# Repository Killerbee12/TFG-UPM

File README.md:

# Sistema de Alimentación Portátil para Montura de Telescopio

**Trabajo Fin de Grado** — Grado en Ingeniería Electrónica de Comunicaciones  
ETSIST · Universidad Politécnica de Madrid (UPM)

---

## De qué va este proyecto

Cualquiera que haya hecho astrofotografía o astronomía visual en campo abierto sabe que la energía es un problema. Las monturas motorizadas, las cámaras y los accesorios necesitan alimentación estable durante horas, normalmente lejos de cualquier enchufe. La solución clásica es cargar con una batería de plomo-ácido, que pesa, ocupa y no te dice cuánta carga le queda realmente.

Este TFG propone una alternativa: un **sistema de alimentación portátil basado en baterías LiFePO4** (12.8V, 7.5Ah), más ligeras y seguras que el plomo, con electrónica dedicada para monitorizar el estado de carga real, gestionar la recarga y entregar una tensión de salida estable a la montura.

## Qué hace el sistema

- **Mide la carga real de la batería** usando un fuel gauge (BQ34Z100-G1) con tecnología Impedance Track, que compensa el envejecimiento de las celdas y mide temperatura con un termistor NTC.
- **Gestiona la recarga** con un cargador buck-boost BQ25792, compatible con USB-PD 3.0.
- **Estabiliza la tensión de salida** mediante un convertidor buck-boost TPS551892-Q1, preparado para los picos de corriente que generan los motores de la montura.
- **Coordina todo** desde un microcontrolador STM32F411 programado con FreeRTOS, que lee la telemetría por I2C y gestiona las tareas del sistema de forma concurrente.

## Diseño hardware

El hardware está diseñado en **KiCad** y separado en PCBs independientes para aislar ruidos electromagnéticos y facilitar la depuración:

1. **Battery Gauge (BMS)** — Circuito del BQ34Z100-G1 con divisor de tensión, shunt de corriente y sensor térmico.
2. **Battery Charger** — Circuito del BQ25792 con la electrónica de carga.
3. **Bloque de control** — MCU STM32F411, buses I2C y lectura de telemetría.

## Estructura del repositorio

```
├── Anteproyecto/          Documentos del anteproyecto (borradores, versión firmada, ejemplos y revisiones del tutor)
├── Archivos/              Datasheets de referencia consultados durante el diseño
├── Inventario/            Datasheets organizados por tipo de componente:
│   ├── Bateria/               Pack LiFePO4 12.8V 7.5Ah
│   ├── Battery_Charger/       BQ25792, BQ25690, LTC4020, etc.
│   ├── Battery_Gauge/         BQ34Z100-G1, BQ34110, BQ78350, etc.
│   ├── DC-DC_BuckBoost/       TPS551892-Q1, TPS55285, TPS63070, etc.
│   ├── Microcontrolador/      STM32F411 Discovery
│   ├── Bobina/
│   ├── Conectores/
│   ├── Diodos-zener/
│   ├── Resistencias/
│   └── Transistores/
├── Notas/                 Notas y documentación del proyecto (memoria, apuntes)
├── PCB/                   Diseños de PCB en KiCad
│   ├── Prototipo_2.0/        Prototipo inicial del battery gauge
│   └── Proyecto/              Diseños finales
│       ├── PCB_BatteryCharger/
│       └── PCB_BatteryGaulge/
├── STM32_project/         Firmware en C (STM32CubeIDE + FreeRTOS)
└── README.md
```

## Herramientas utilizadas

| Área | Herramienta |
|---|---|
| Esquemáticos y PCB | KiCad |
| Firmware | STM32CubeIDE (HAL + FreeRTOS) |
| Microcontrolador | STM32F411 Discovery |
| Documentación | Word / PDF |

## Estado del proyecto

Este repositorio recoge todo el proceso de desarrollo del TFG: desde los primeros borradores del anteproyecto hasta los diseños de PCB y el firmware. Es un proyecto en progreso.

---

*Nizar El Azeouzi Amine — ETSIST, Universidad Politécnica de Madrid*

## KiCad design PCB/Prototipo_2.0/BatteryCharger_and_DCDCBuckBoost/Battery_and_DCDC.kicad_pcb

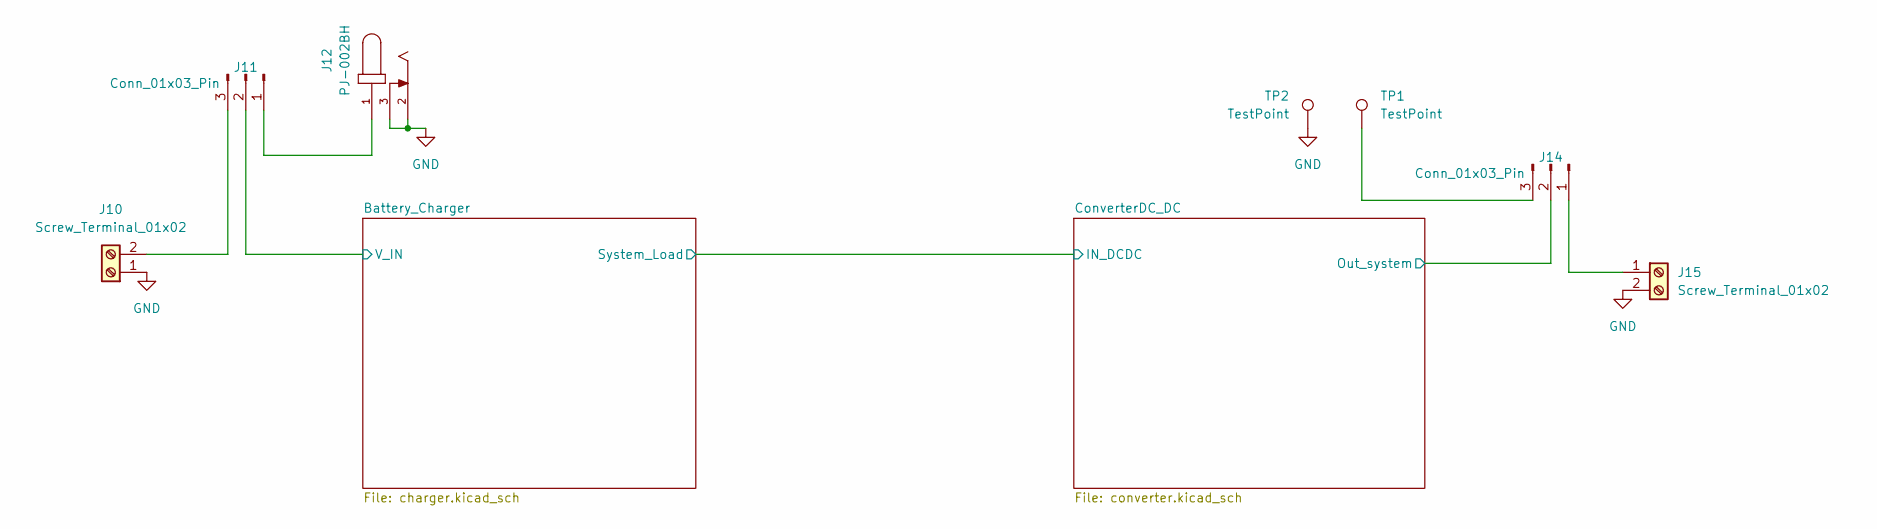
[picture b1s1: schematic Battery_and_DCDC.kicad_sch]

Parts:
J10, J15: Screw_Terminal_01x02; TerminalBlock_Phoenix_MKDS-1,5-2_1x02_P5.00mm_Horizontal
J11, J14: Conn_01x03_Pin; PinHeader_1x03_P2.54mm_Vertical
J12: PJ-002BH; CUI_PJ-002BH
TP1, TP2: TestPoint; TestPoint_Pad_3.0x3.0mm

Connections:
/Battery_Charger/V_IN: J11.2; also elsewhere on the board
/ConverterDC_DC/Out_system: J14.2; also elsewhere on the board
GND: J10.1, J12.2, J12.3, J15.2, TP2.1; also elsewhere on the board
unnamed: J10.2, J11.3
unnamed: J11.1, J12.1
unnamed: J14.1, J15.1
unnamed: J14.3, TP1.1

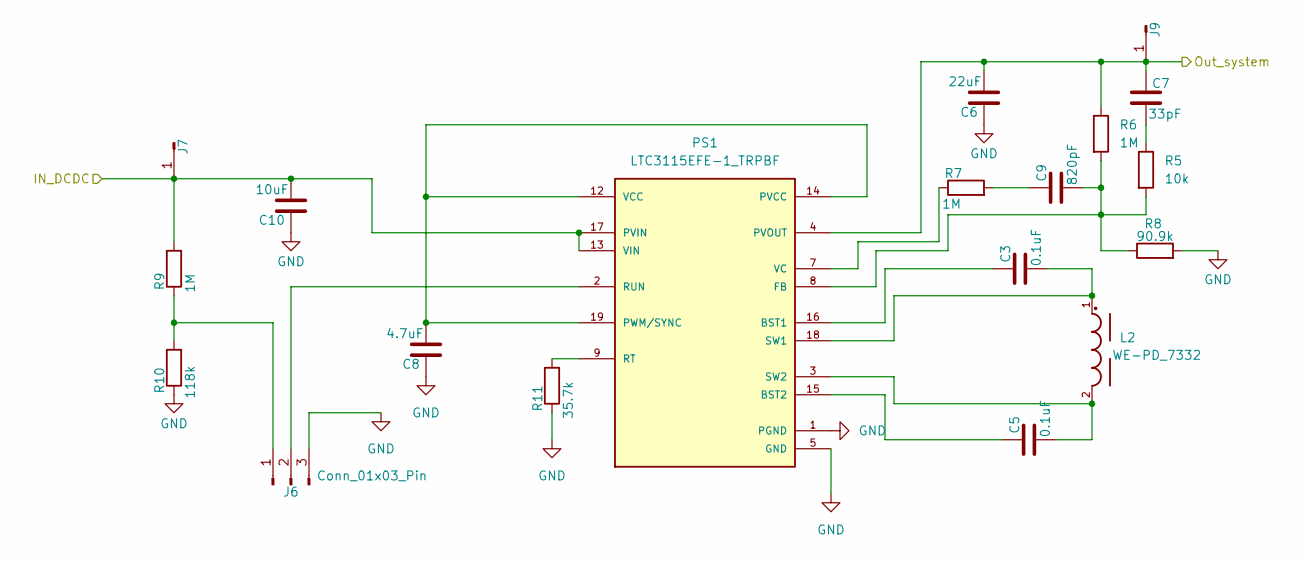
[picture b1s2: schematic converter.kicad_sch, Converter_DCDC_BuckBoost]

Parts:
C3, C5: 0.1uF; C_1206_3216Metric_Pad1.33x1.80mm_HandSolder
C6: 22uF; C_1206_3216Metric_Pad1.33x1.80mm_HandSolder
C7: 33pF; C_1206_3216Metric_Pad1.33x1.80mm_HandSolder
C8: 4.7uF; C_1206_3216Metric_Pad1.33x1.80mm_HandSolder
C9: 820pF; C_1206_3216Metric_Pad1.33x1.80mm_HandSolder
C10: 10uF; C_1206_3216Metric_Pad1.33x1.80mm_HandSolder
J6: Conn_01x03_Pin; PinHeader_1x03_P2.54mm_Vertical
J7, J9: Conn_01x01_Pin; PinHeader_1x01_P2.54mm_Vertical
L2: WE-PD_7332
PS1: LTC3115EFE-1_TRPBF; CONV_LTC3115EFE-1_TRPBF; PARTREV E
R5: 10k; R_1206_3216Metric_Pad1.30x1.75mm_HandSolder
R6, R7, R9: 1M; R_1206_3216Metric_Pad1.30x1.75mm_HandSolder
R8: 90.9k; R_1206_3216Metric_Pad1.30x1.75mm_HandSolder
R10: 118k; R_1206_3216Metric_Pad1.30x1.75mm_HandSolder
R11: 35.7k; R_1206_3216Metric_Pad1.30x1.75mm_HandSolder

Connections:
/Battery_Charger/System_Load: C10.1, J7.1, PS1.13 (VIN), PS1.17 (PVIN), R9.2; also elsewhere on the board
/ConverterDC_DC/Out_system: C6.1, C7.2, J9.1, PS1.4 (PVOUT), R6.1; also elsewhere on the board
GND: C6.2, C8.2, C10.2, J6.3, PS1.1 (PGND), PS1.5 (GND), PS1.6 (GND), PS1.10 (PGND), PS1.11 (PGND), PS1.20 (PGND), PS1.21 (PGND), R8.2, R10.1, R11.1; also elsewhere on the board
unnamed: C7.1, R5.1
unnamed: C9.2, R7.2
unnamed: J6.1, R9.1, R10.2
unnamed: J6.2, PS1.2 (RUN)
unnamed: C3.2, PS1.16 (BST1)
unnamed: C5.2, PS1.15 (BST2)
unnamed: C9.1, PS1.8 (FB), R5.2, R6.2, R8.1
unnamed: C8.1, PS1.12 (VCC), PS1.14 (PVCC), PS1.19 (PWM/SYNC)
unnamed: PS1.9 (RT), R11.2
unnamed: C3.1, L2.1, PS1.18 (SW1)
unnamed: C5.1, L2.2, PS1.3 (SW2)
unnamed: PS1.7 (VC), R7.1

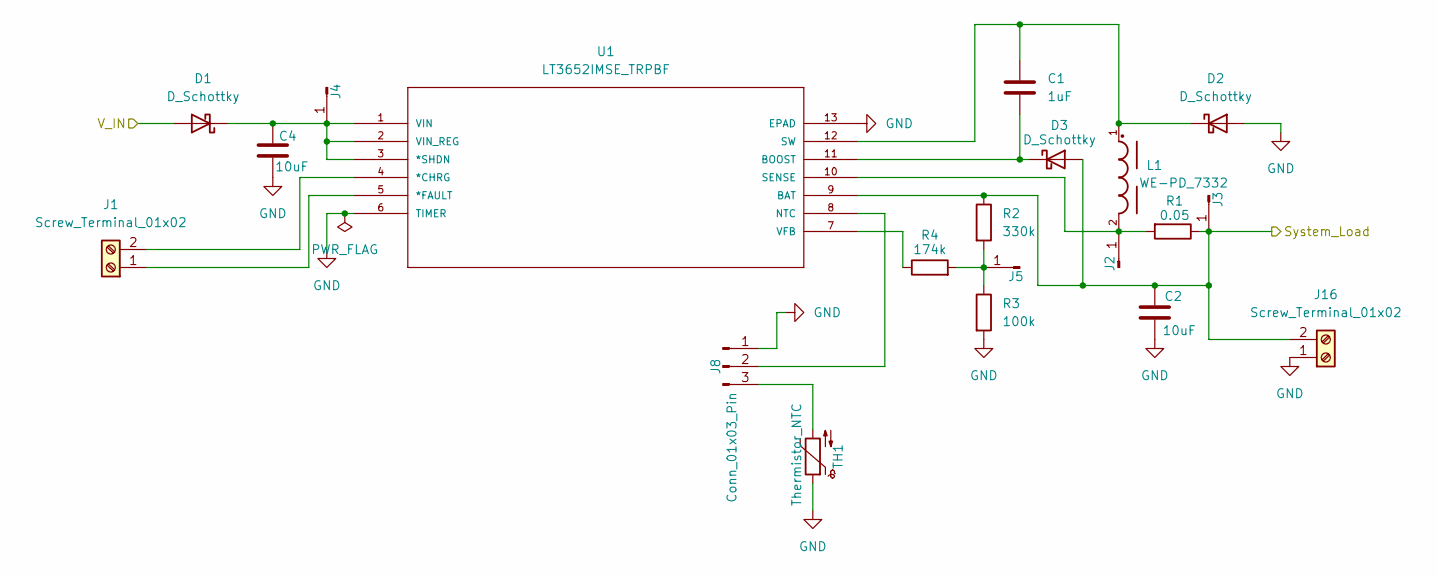
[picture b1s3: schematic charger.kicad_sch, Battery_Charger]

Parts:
C1: 1uF; C_1206_3216Metric_Pad1.33x1.80mm_HandSolder
C2, C4: 10uF; C_1206_3216Metric_Pad1.33x1.80mm_HandSolder
D1, D2: D_Schottky; D_SMB
D3: D_Schottky; D_SOD-123
J1, J16: Screw_Terminal_01x02; TerminalBlock_Phoenix_MKDS-1,5-2_1x02_P5.00mm_Horizontal
J2, J3, J4, J5: Conn_01x01_Pin; PinHeader_1x01_P2.54mm_Vertical
J8: Conn_01x03_Pin; PinHeader_1x03_P2.54mm_Vertical
L1: WE-PD_7332
R1: 0.05; R_1206_3216Metric_Pad1.30x1.75mm_HandSolder
R2: 330k; R_1206_3216Metric_Pad1.30x1.75mm_HandSolder
R3: 100k; R_1206_3216Metric_Pad1.30x1.75mm_HandSolder
R4: 174k; R_1206_3216Metric_Pad1.30x1.75mm_HandSolder
TH1: Thermistor_NTC; R_Axial_DIN0204_L3.6mm_D1.6mm_P5.08mm_Horizontal
U1: LT3652IMSE_TRPBF; MSOP-12_MSE; MANUFACTURER_PART_NUMBER lt3652imse#pbf

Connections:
/Battery_Charger/System_Load: C2.2, D3.2 (A), J3.1, J16.2, R1.1, R2.1, U1.9 (BAT); also elsewhere on the board
/Battery_Charger/V_IN: D1.2 (A); also elsewhere on the board
GND: C2.1, C4.1, D2.2 (A), J8.1, J16.1, R3.2, TH1.1, U1.6 (TIMER), U1.13 (EPAD); also elsewhere on the board
unnamed: C4.2, D1.1 (K), J4.1, U1.1 (VIN), U1.2 (VIN_REG), U1.3 (*SHDN)
unnamed: C1.2, D2.1 (K), L1.1, U1.12 (SW)
unnamed: C1.1, D3.1 (K), U1.11 (BOOST)
unnamed: J1.1, U1.5 (*FAULT)
unnamed: J1.2, U1.4 (*CHRG)
unnamed: J2.1, L1.2, R1.2, U1.10 (SENSE)
unnamed: J5.1, R2.2, R3.1, R4.2
unnamed: J8.2, U1.8 (NTC)
unnamed: J8.3, TH1.2
unnamed: R4.1, U1.7 (VFB)

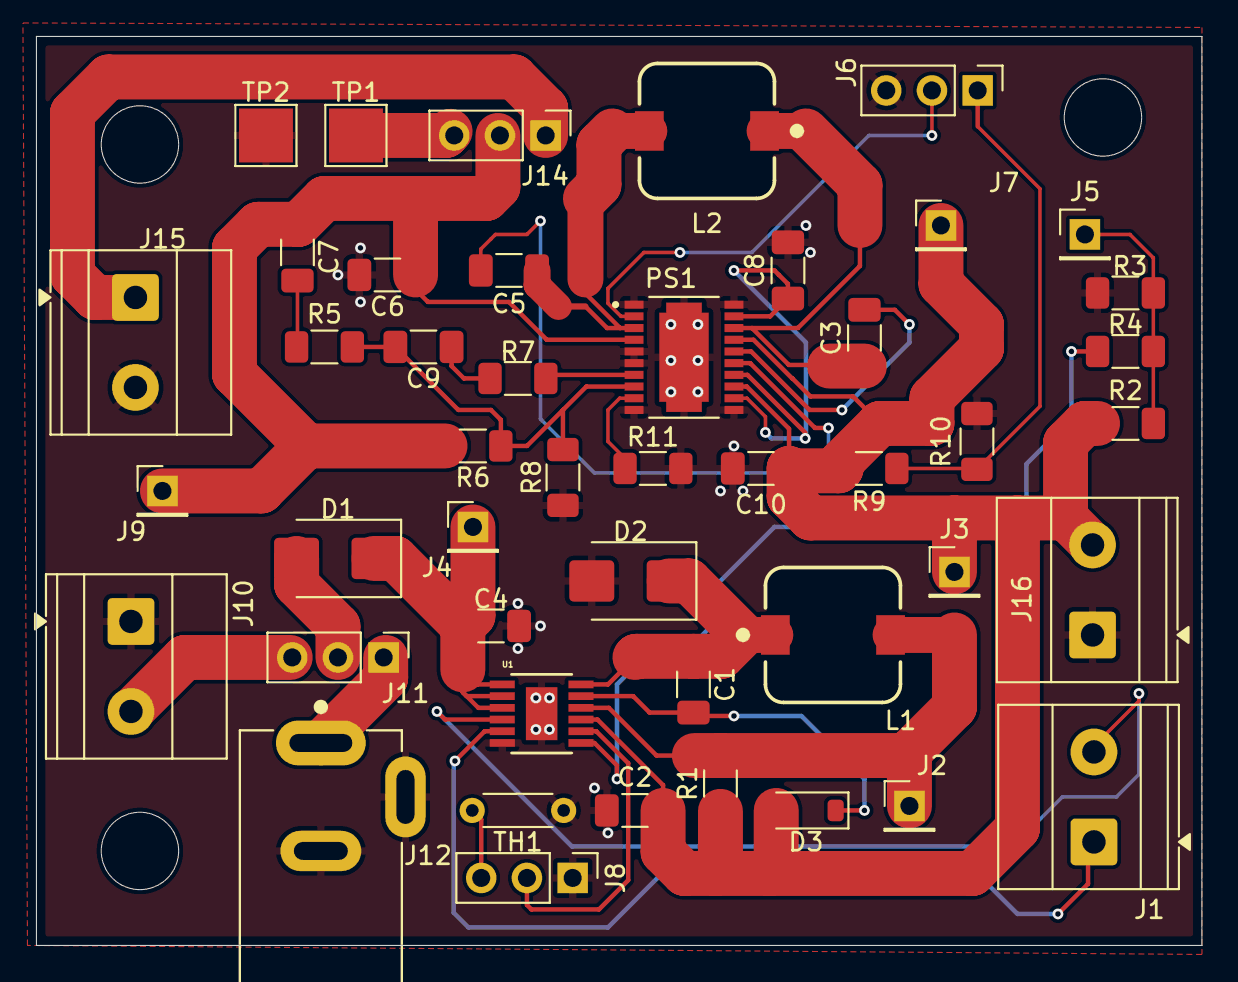
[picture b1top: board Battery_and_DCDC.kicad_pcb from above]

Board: 2 copper layers, 64.8 x 50.5 mm, 49 parts (0 on the bottom side), 30 nets.

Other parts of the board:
M1, M1#2, M1#3: MountingHole_4.3mm_M4

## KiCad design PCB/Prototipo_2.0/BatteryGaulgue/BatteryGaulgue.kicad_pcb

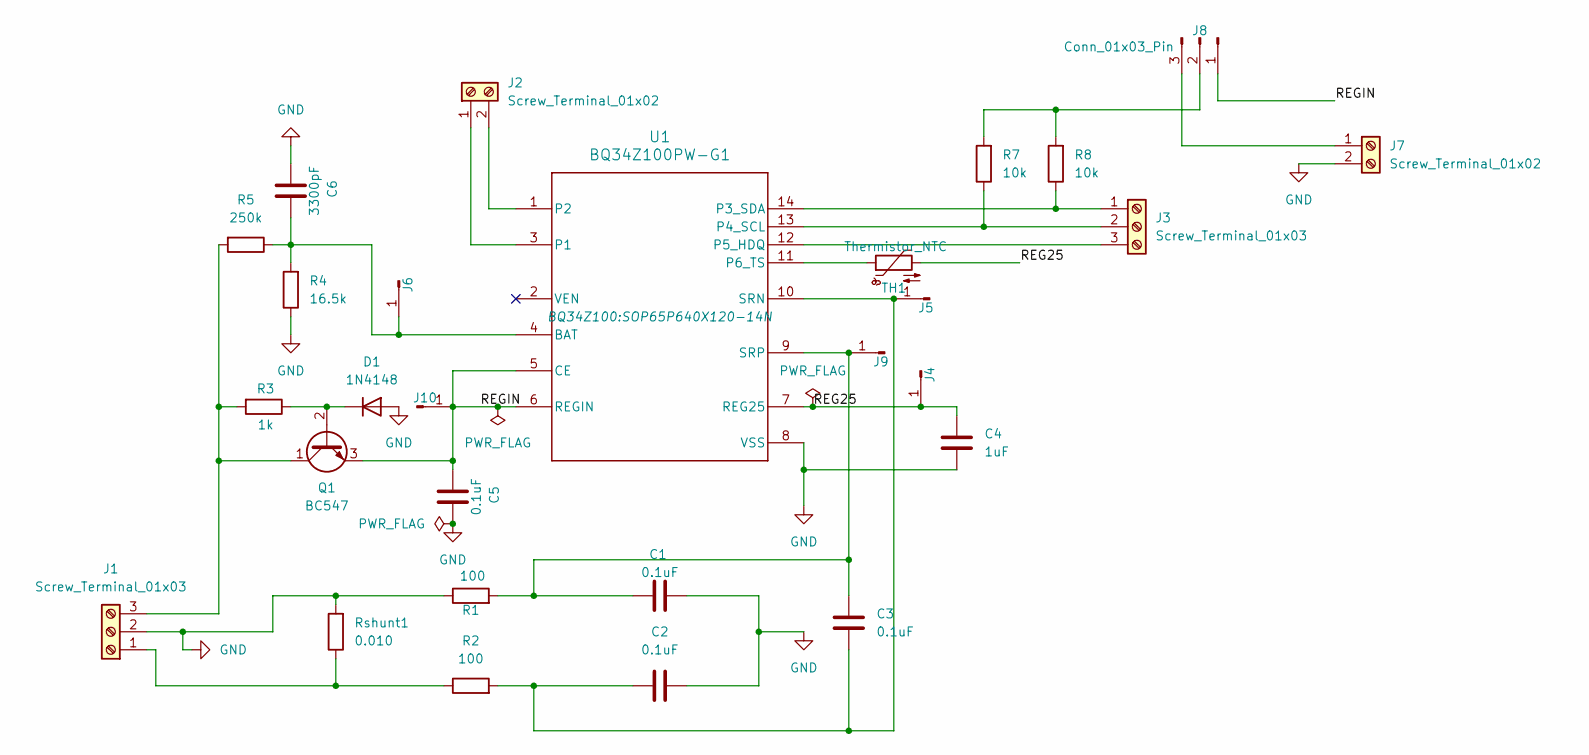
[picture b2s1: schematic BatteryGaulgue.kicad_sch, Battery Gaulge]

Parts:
C1, C2, C3, C5: 0.1uF; C_0805_2012Metric_Pad1.18x1.45mm_HandSolder
C4: 1uF; C_0805_2012Metric_Pad1.18x1.45mm_HandSolder
C6: 3300pF; C_0805_2012Metric_Pad1.18x1.45mm_HandSolder
D1: 1N4148; D_DO-35_SOD27_P7.62mm_Horizontal
J1, J3: Screw_Terminal_01x03; TerminalBlock_Phoenix_MKDS-1,5-3_1x03_P5.00mm_Horizontal
J2, J7: Screw_Terminal_01x02; TerminalBlock_Phoenix_MKDS-1,5-2_1x02_P5.00mm_Horizontal
J4, J5, J6, J9, J10: Conn_01x01_Pin; PinHeader_1x01_P2.54mm_Vertical
J8: Conn_01x03_Pin; PinHeader_1x03_P2.54mm_Vertical
Q1: BC547; TO-92_Inline
R1, R2: 100; R_1206_3216Metric_Pad1.30x1.75mm_HandSolder
R3: 1k; R_1206_3216Metric_Pad1.30x1.75mm_HandSolder
R4: 16.5k; R_1206_3216Metric_Pad1.30x1.75mm_HandSolder
R5: 250k; R_1206_3216Metric_Pad1.30x1.75mm_HandSolder
R7, R8: 10k; R_1206_3216Metric_Pad1.30x1.75mm_HandSolder
Rshunt1: 0.010; R_2512_6332Metric_Pad1.40x3.35mm_HandSolder
TH1: Thermistor_NTC; R_Axial_DIN0204_L3.6mm_D1.6mm_P5.08mm_Horizontal
U1: BQ34Z100PW-G1; SOP65P640X120-14N

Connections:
/REG25: C4.2, J4.1, TH1.2, U1.7 (REG25)
/REGIN: C5.2, J8.1, J10.1, Q1.3 (E), U1.5 (CE), U1.6 (REGIN)
GND: C1.1, C2.1, C4.1, C5.1, C6.2, D1.2 (A), J1.2, J7.2, R1.1, R4.1, Rshunt1.2, U1.8 (VSS)
unnamed: D1.1 (K), Q1.2 (B), R3.1
unnamed: J1.1, R2.1, Rshunt1.1
unnamed: J1.3, Q1.1 (C), R3.2, R5.2
unnamed: J2.1, U1.3 (P1)
unnamed: J2.2, U1.1 (P2)
unnamed: J3.1, R8.1, U1.14 (P3_SDA)
unnamed: J3.2, R7.1, U1.13 (P4_SCL)
unnamed: J3.3, U1.12 (P5_HDQ)
unnamed: C2.2, C3.2, J5.1, R2.2, U1.10 (SRN)
unnamed: C6.1, J6.1, R4.2, R5.1, U1.4 (BAT)
unnamed: J7.1, J8.3
unnamed: J8.2, R7.2, R8.2
unnamed: C1.2, C3.1, J9.1, R1.2, U1.9 (SRP)
unnamed: TH1.1, U1.11 (P6_TS)

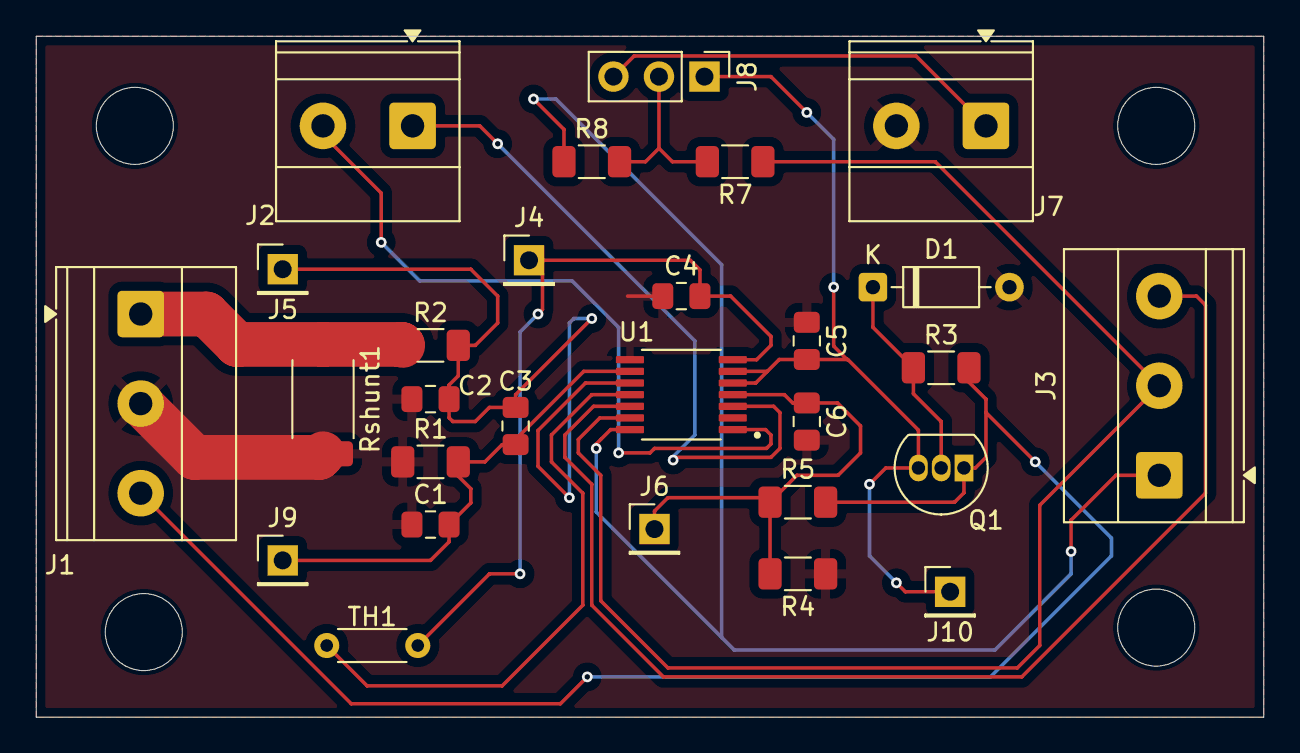
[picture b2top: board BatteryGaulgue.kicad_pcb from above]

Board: 2 copper layers, 68.5 x 38.0 mm, 32 parts (0 on the bottom side), 17 nets.

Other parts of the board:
M1, M2, M3, M4: MountingHole_4.3mm_M4

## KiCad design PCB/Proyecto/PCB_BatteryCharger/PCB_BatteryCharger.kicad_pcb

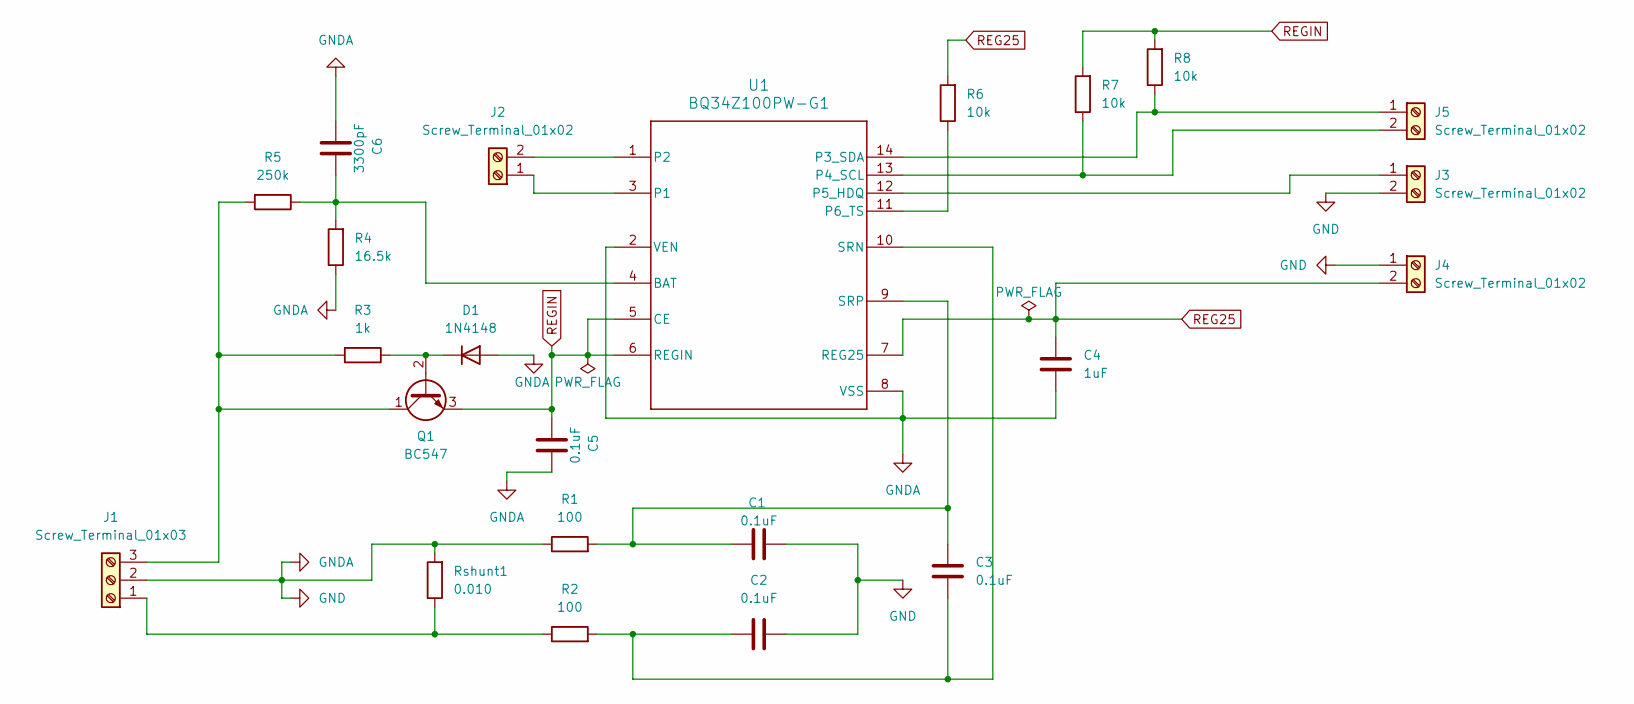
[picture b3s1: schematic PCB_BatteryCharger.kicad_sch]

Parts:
C1, C2, C3, C5: 0.1uF; C_Rect_L7.0mm_W3.5mm_P5.00mm
C4: 1uF; C_Rect_L7.0mm_W3.5mm_P5.00mm
C6: 3300pF; C_Rect_L7.0mm_W3.5mm_P5.00mm
D1: 1N4148; D_DO-35_SOD27_P7.62mm_Horizontal
J1: Screw_Terminal_01x03; TerminalBlock_Phoenix_MKDS-1-3-3.81_1x03_P3.81mm_Horizontal
J2, J3, J4, J5: Screw_Terminal_01x02; TerminalBlock_Phoenix_MKDS-1-2-3.81_1x02_P3.81mm_Horizontal
Q1: BC547; TO-92_Inline
R1, R2: 100; R_Axial_DIN0207_L6.3mm_D2.5mm_P10.16mm_Horizontal
R3: 1k; R_Axial_DIN0207_L6.3mm_D2.5mm_P10.16mm_Horizontal
R4: 16.5k; R_Axial_DIN0207_L6.3mm_D2.5mm_P10.16mm_Horizontal
R5: 250k; R_Axial_DIN0207_L6.3mm_D2.5mm_P10.16mm_Horizontal
R6, R7, R8: 10k; R_Axial_DIN0207_L6.3mm_D2.5mm_P10.16mm_Horizontal
Rshunt1: 0.010; R_2512_6332Metric_Pad1.40x3.35mm_HandSolder
U1: BQ34Z100PW-G1; PW0014A_N

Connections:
GND: C1.1, C2.1, C4.1, C5.1, C6.2, D1.2 (A), J1.2, J3.2, J4.1, R1.1, R4.1, Rshunt1.2, U1.2 (VEN), U1.8 (VSS)
unnamed: D1.1 (K), Q1.2 (B), R3.1
unnamed: J1.1, R2.1, Rshunt1.1
unnamed: J1.3, Q1.1 (C), R3.2, R5.2
unnamed: J2.1, U1.3 (P1)
unnamed: J2.2, U1.1 (P2)
unnamed: J3.1, U1.12 (P5_HDQ)
unnamed: J5.1, R8.1, U1.14 (P3_SDA)
unnamed: J5.2, R7.1, U1.13 (P4_SCL)
unnamed: C6.1, R4.2, R5.1, U1.4 (BAT)
unnamed: R6.1, U1.11 (P6_TS)
unnamed: C2.2, C3.2, R2.2, U1.10 (SRN)
unnamed: C1.2, C3.1, R1.2, U1.9 (SRP)
REG25: C4.2, J4.2, R6.2, U1.7 (REG25)
REGIN: C5.2, Q1.3 (E), R7.2, R8.2, U1.5 (CE), U1.6 (REGIN)

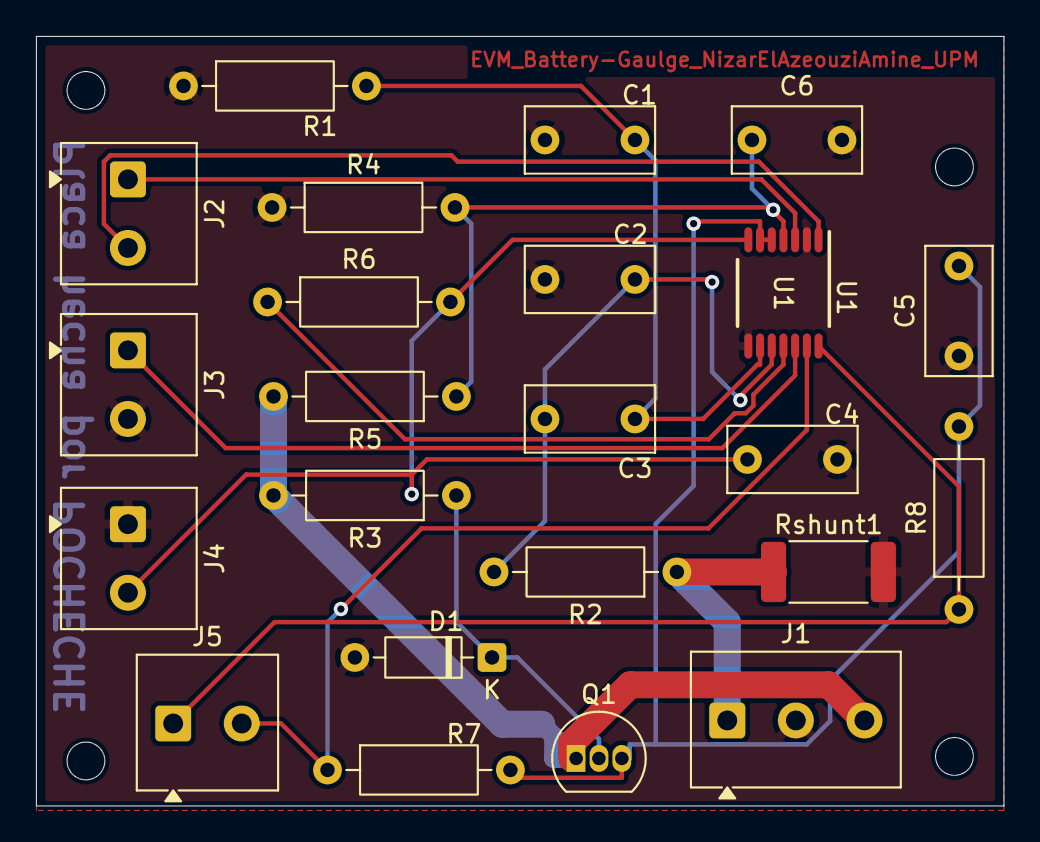
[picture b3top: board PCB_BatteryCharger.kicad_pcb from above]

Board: 2 copper layers, 53.8 x 42.8 mm, 27 parts (0 on the bottom side), 15 nets.

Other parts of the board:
H1, H2, H3, H4: MountingHole_2.1mm

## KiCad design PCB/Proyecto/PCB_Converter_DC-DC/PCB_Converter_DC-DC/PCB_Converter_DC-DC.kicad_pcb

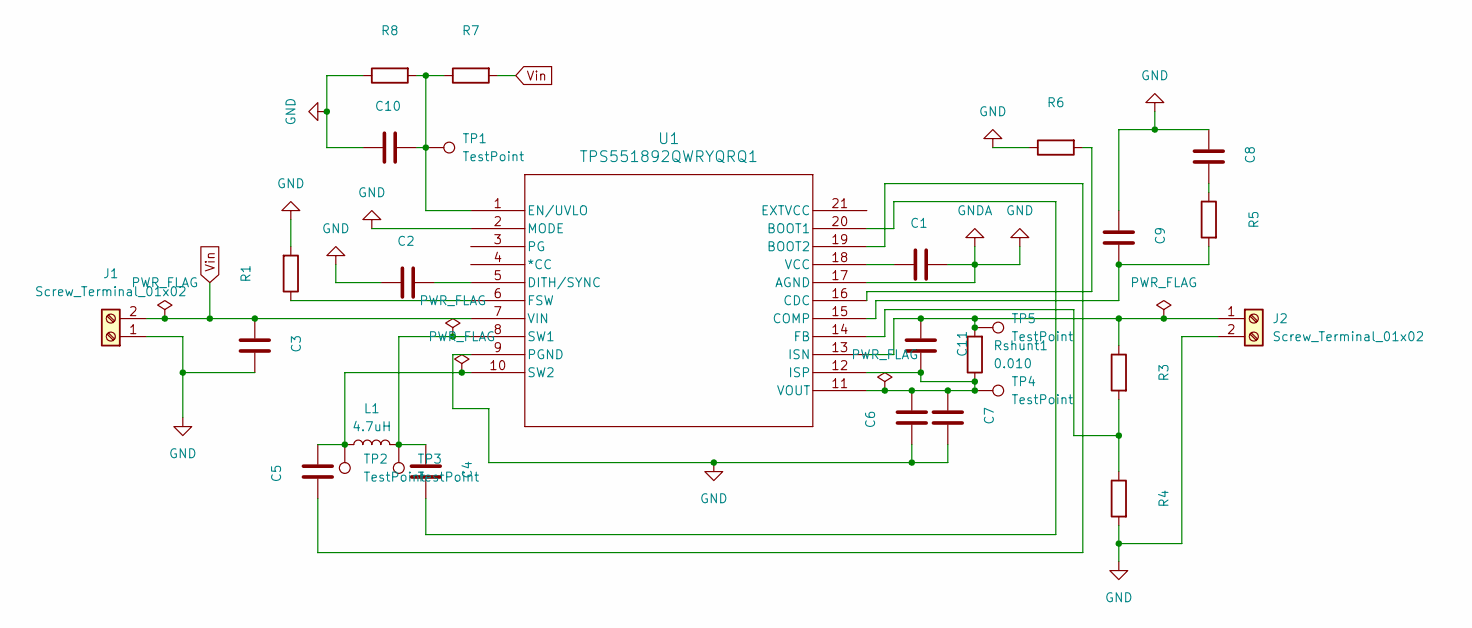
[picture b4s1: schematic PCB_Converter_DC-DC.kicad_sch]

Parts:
C1, C2, C3, C4, C5, C6, C7, C8, C9, C10, C11: C_Rect_L7.0mm_W3.5mm_P5.00mm
J1, J2: Screw_Terminal_01x02; TerminalBlock_Phoenix_MKDS-1-2-3.81_1x02_P3.81mm_Horizontal
L1: 4.7uH; L_Radial_D10.0mm_P5.00mm_Fastron_07M
R1, R3, R4, R5, R6, R7, R8: R_Axial_DIN0207_L6.3mm_D2.5mm_P10.16mm_Horizontal
Rshunt1: 0.010; R_2512_6332Metric_Pad1.40x3.35mm_HandSolder
TP1, TP2, TP3, TP4, TP5: TestPoint; TestPoint_THTPad_D2.0mm_Drill1.0mm
U1: TPS551892QWRYQRQ1; VQFN21_RYQ_TEX

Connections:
GND: C1.1, C2.2, C3.1, C6.2, C7.1, C8.2, C9.2, C10.2, J1.1, J2.2, R1.2, R4.2, R6.1, R8.1, U1.2 (MODE), U1.9 (PGND), U1.17 (AGND)
unnamed: C8.1, R5.1
unnamed: C11.2, J2.1, R3.1, Rshunt1.2, TP5.1, U1.13 (ISN)
unnamed: C4.1, U1.20 (BOOT1)
unnamed: C5.2, U1.19 (BOOT2)
unnamed: R6.2, U1.16 (CDC)
unnamed: C9.1, R5.2, U1.15 (COMP)
unnamed: C2.1, U1.5 (DITH/SYNC)
unnamed: C10.1, R7.1, R8.2, TP1.1, U1.1 (EN/UVLO)
unnamed: R3.2, R4.1, U1.14 (FB)
unnamed: R1.1, U1.6 (FSW)
unnamed: C6.1, C7.2, C11.1, Rshunt1.1, TP4.1, U1.11 (VOUT), U1.12 (ISP)
unnamed: C4.2, L1.2, TP3.1, U1.8 (SW1)
unnamed: C5.1, L1.1, TP2.1, U1.10 (SW2)
unnamed: C1.2, U1.18 (VCC)
Vin: C3.2, J1.2, R7.2, U1.7 (VIN)

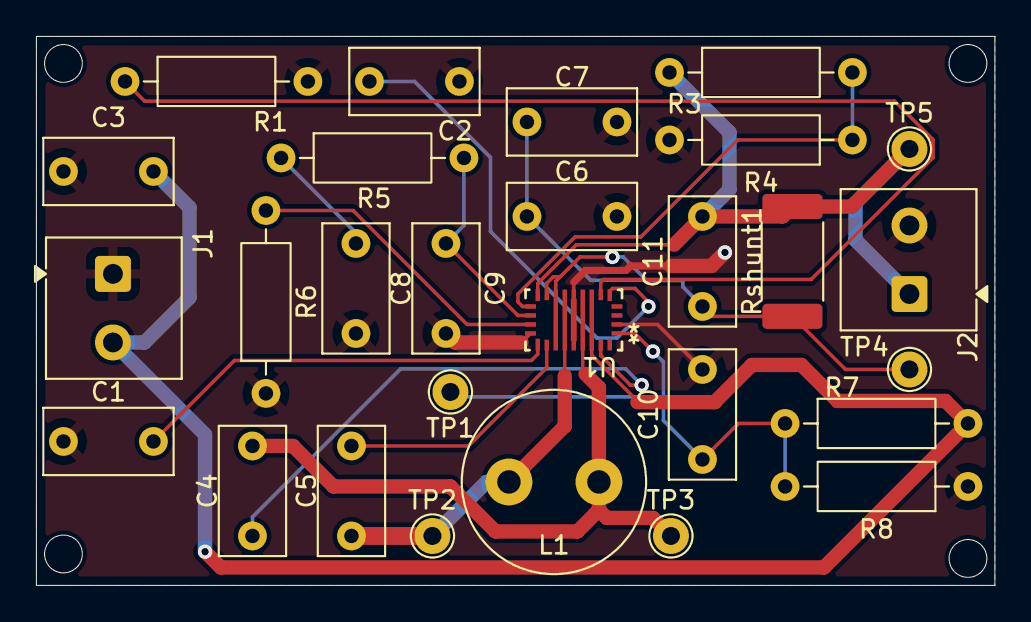
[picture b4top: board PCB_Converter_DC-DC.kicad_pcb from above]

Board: 2 copper layers, 53.2 x 30.5 mm, 32 parts (0 on the bottom side), 16 nets.

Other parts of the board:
H2, H3, H4, H5: MountingHole_2.1mm

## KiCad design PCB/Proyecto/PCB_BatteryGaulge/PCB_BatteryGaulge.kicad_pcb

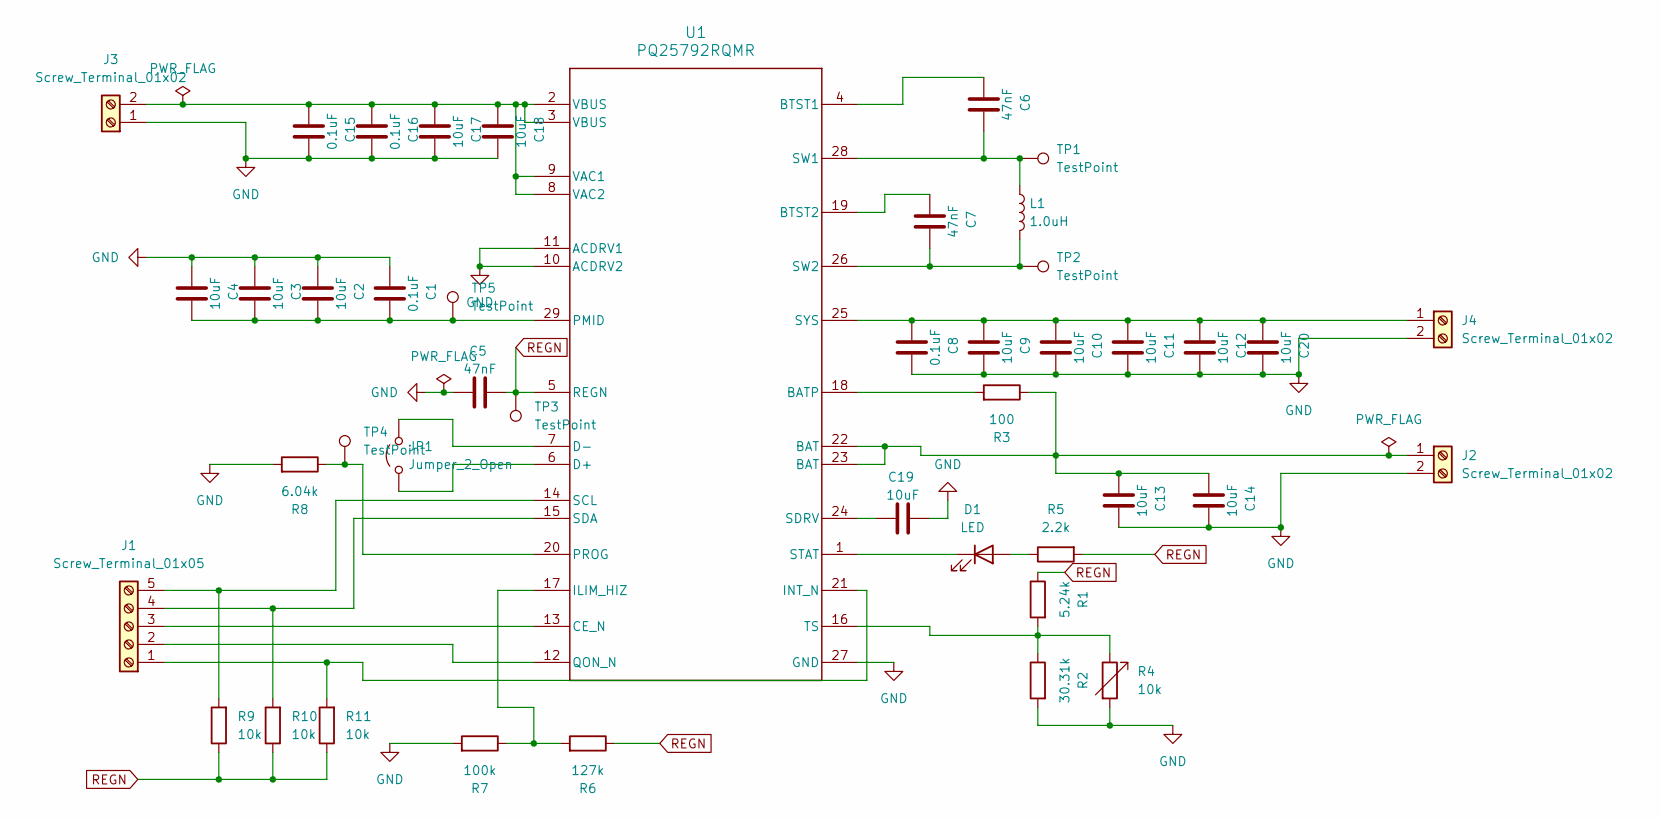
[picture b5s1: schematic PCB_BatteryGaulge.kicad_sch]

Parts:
C1, C8, C15, C16: 0.1uF; C_Rect_L7.0mm_W3.5mm_P5.00mm
C2, C3, C4, C9, C10, C11, C12, C13, C14, C17, C18, C19, C20: 10uF; C_Rect_L7.0mm_W3.5mm_P5.00mm
C5, C6, C7: 47nF; C_Rect_L7.0mm_W3.5mm_P5.00mm
D1: LED; LED_D3.0mm
J1: Screw_Terminal_01x05; TerminalBlock_Phoenix_MKDS-1-5-3.81_1x05_P3.81mm_Horizontal
J2, J3, J4: Screw_Terminal_01x02; TerminalBlock_Phoenix_MKDS-1-2-3.81_1x02_P3.81mm_Horizontal
JP1: Jumper_2_Open; TestPoint_2Pads_Pitch2.54mm_Drill0.8mm
L1: 1.0uH; L_Radial_D10.0mm_P5.00mm_Fastron_07M
R1: 5.24k; R_Axial_DIN0207_L6.3mm_D2.5mm_P10.16mm_Horizontal
R2: 30.31k; R_Axial_DIN0207_L6.3mm_D2.5mm_P10.16mm_Horizontal
R3: 100; R_Axial_DIN0207_L6.3mm_D2.5mm_P10.16mm_Horizontal
R4: 10k; R_Axial_DIN0207_L6.3mm_D2.5mm_P7.62mm_Horizontal
R5: 2.2k; R_Axial_DIN0207_L6.3mm_D2.5mm_P10.16mm_Horizontal
R6: 127k; R_Axial_DIN0207_L6.3mm_D2.5mm_P10.16mm_Horizontal
R7: 100k; R_Axial_DIN0207_L6.3mm_D2.5mm_P10.16mm_Horizontal
R8: 6.04k; R_Axial_DIN0207_L6.3mm_D2.5mm_P10.16mm_Horizontal
R9, R10, R11: 10k; R_Axial_DIN0207_L6.3mm_D2.5mm_P10.16mm_Horizontal
TP1, TP2, TP3, TP4, TP5: TestPoint; TestPoint_THTPad_D2.0mm_Drill1.0mm
U1: PQ25792RQMR; RQM0029A-MFG

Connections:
GND: C1.2, C2.2, C3.2, C4.2, C5.2, C8.1, C9.1, C10.1, C11.1, C12.1, C13.1, C14.1, C15.1, C16.1, C17.1, C18.1, C19.1, C20.1, J2.2, J3.1, J4.2, R2.2, R4.2, R7.2, R8.2, U1.10 (ACDRV2), U1.11 (ACDRV1), U1.27 (GND)
unnamed: D1.2 (A), R5.1
unnamed: D1.1 (K), U1.1 (STAT)
unnamed: J1.1, R11.2, U1.21 (INT_N)
unnamed: J1.2, U1.12 (QON_N)
unnamed: J1.3, U1.13 (CE_N)
unnamed: J1.4, R10.2, U1.15 (SDA)
unnamed: J1.5, R9.2, U1.14 (SCL)
unnamed: C13.2, C14.2, J2.1, R3.1, U1.22 (BAT), U1.23 (BAT)
unnamed: C15.2, C16.2, C17.2, C18.2, J3.2, U1.2 (VBUS), U1.3 (VBUS), U1.8 (VAC2), U1.9 (VAC1)
unnamed: C8.2, C9.2, C10.2, C11.2, C12.2, C20.2, J4.1, U1.25 (SYS)
unnamed: JP1.1 (A), U1.6 (D+)
unnamed: JP1.2 (B), U1.7 (D-)
unnamed: R3.2, U1.18 (BATP)
unnamed: C6.2, U1.4 (BTST1)
unnamed: C7.2, U1.19 (BTST2)
unnamed: R6.2, R7.1, U1.17 (ILIM_HIZ)
unnamed: C1.1, C2.1, C3.1, C4.1, TP5.1, U1.29 (PMID)
unnamed: R8.1, TP4.1, U1.20 (PROG)
unnamed: C19.2, U1.24 (SDRV)
unnamed: C6.1, L1.1, TP1.1, U1.28 (SW1)
unnamed: C7.1, L1.2, TP2.1, U1.26 (SW2)
unnamed: R1.2, R2.1, R4.1, U1.16 (TS)
REGN: C5.1, R1.1, R5.2, R6.1, R9.1, R10.1, R11.1, TP3.1, U1.5 (REGN)

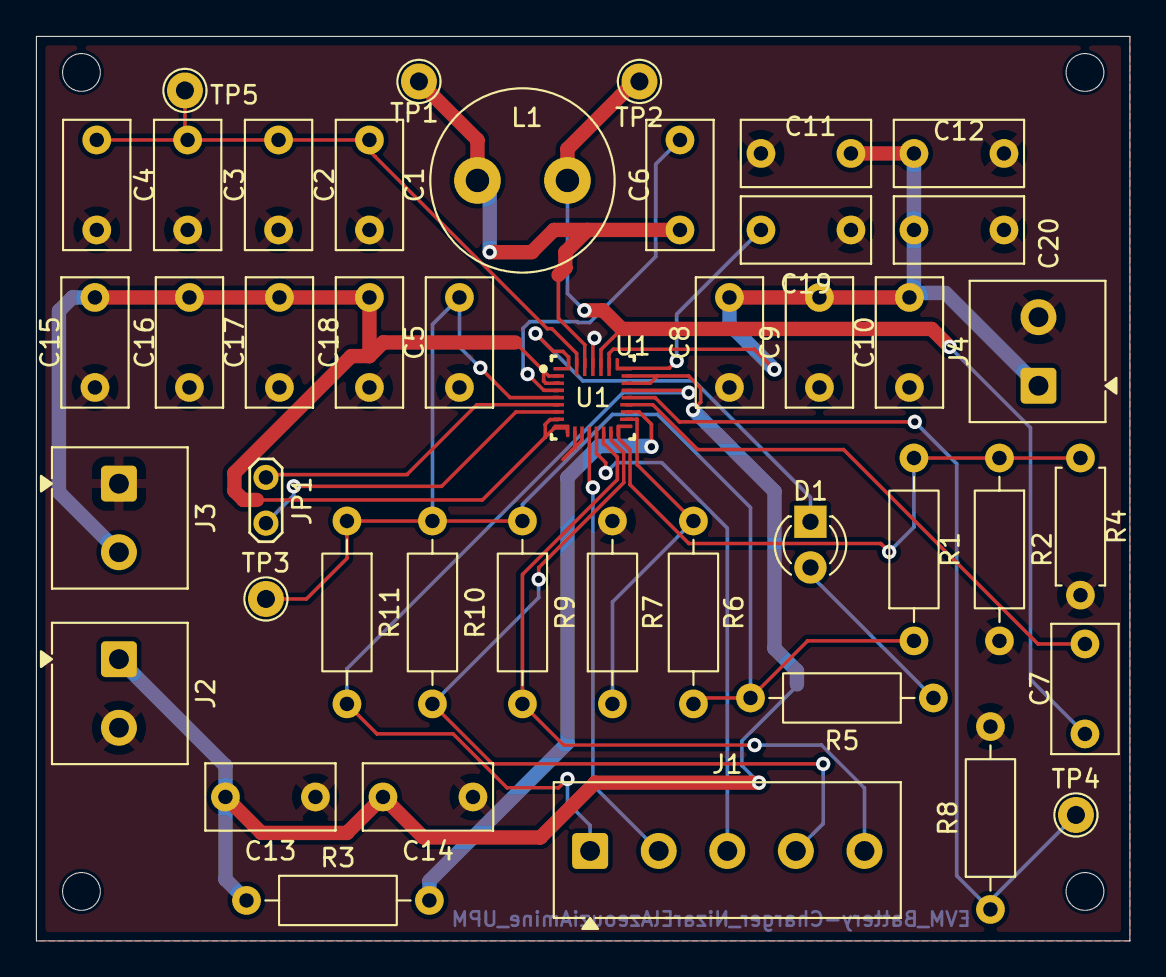
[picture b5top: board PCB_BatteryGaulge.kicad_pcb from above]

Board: 2 copper layers, 60.8 x 50.2 mm, 48 parts (0 on the bottom side), 24 nets.

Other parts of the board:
H1, H1#2, H2, H3: MountingHole_2.1mm

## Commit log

2026-05-07 Subida de proyecto
2026-05-07 Organizacion documentos
2026-05-08 Actualizacion LCD
2026-05-11 Actualizacion proyecto stm32 con lecturas y escritura
2026-05-24 Prototipo del battery gaulge PCB subido
2026-05-24 Initialize README with project details and structure
    Added detailed project description, features, architecture, and repository structure.
2026-05-24 Revise README for project clarity and organization
    Updated README to enhance project description and structure.
2026-05-29 Prototipos de la PCB del batteryGaulgue(falta rootear)
2026-05-30 Placa PCB BatteryGaulgue terminada para fabricar
